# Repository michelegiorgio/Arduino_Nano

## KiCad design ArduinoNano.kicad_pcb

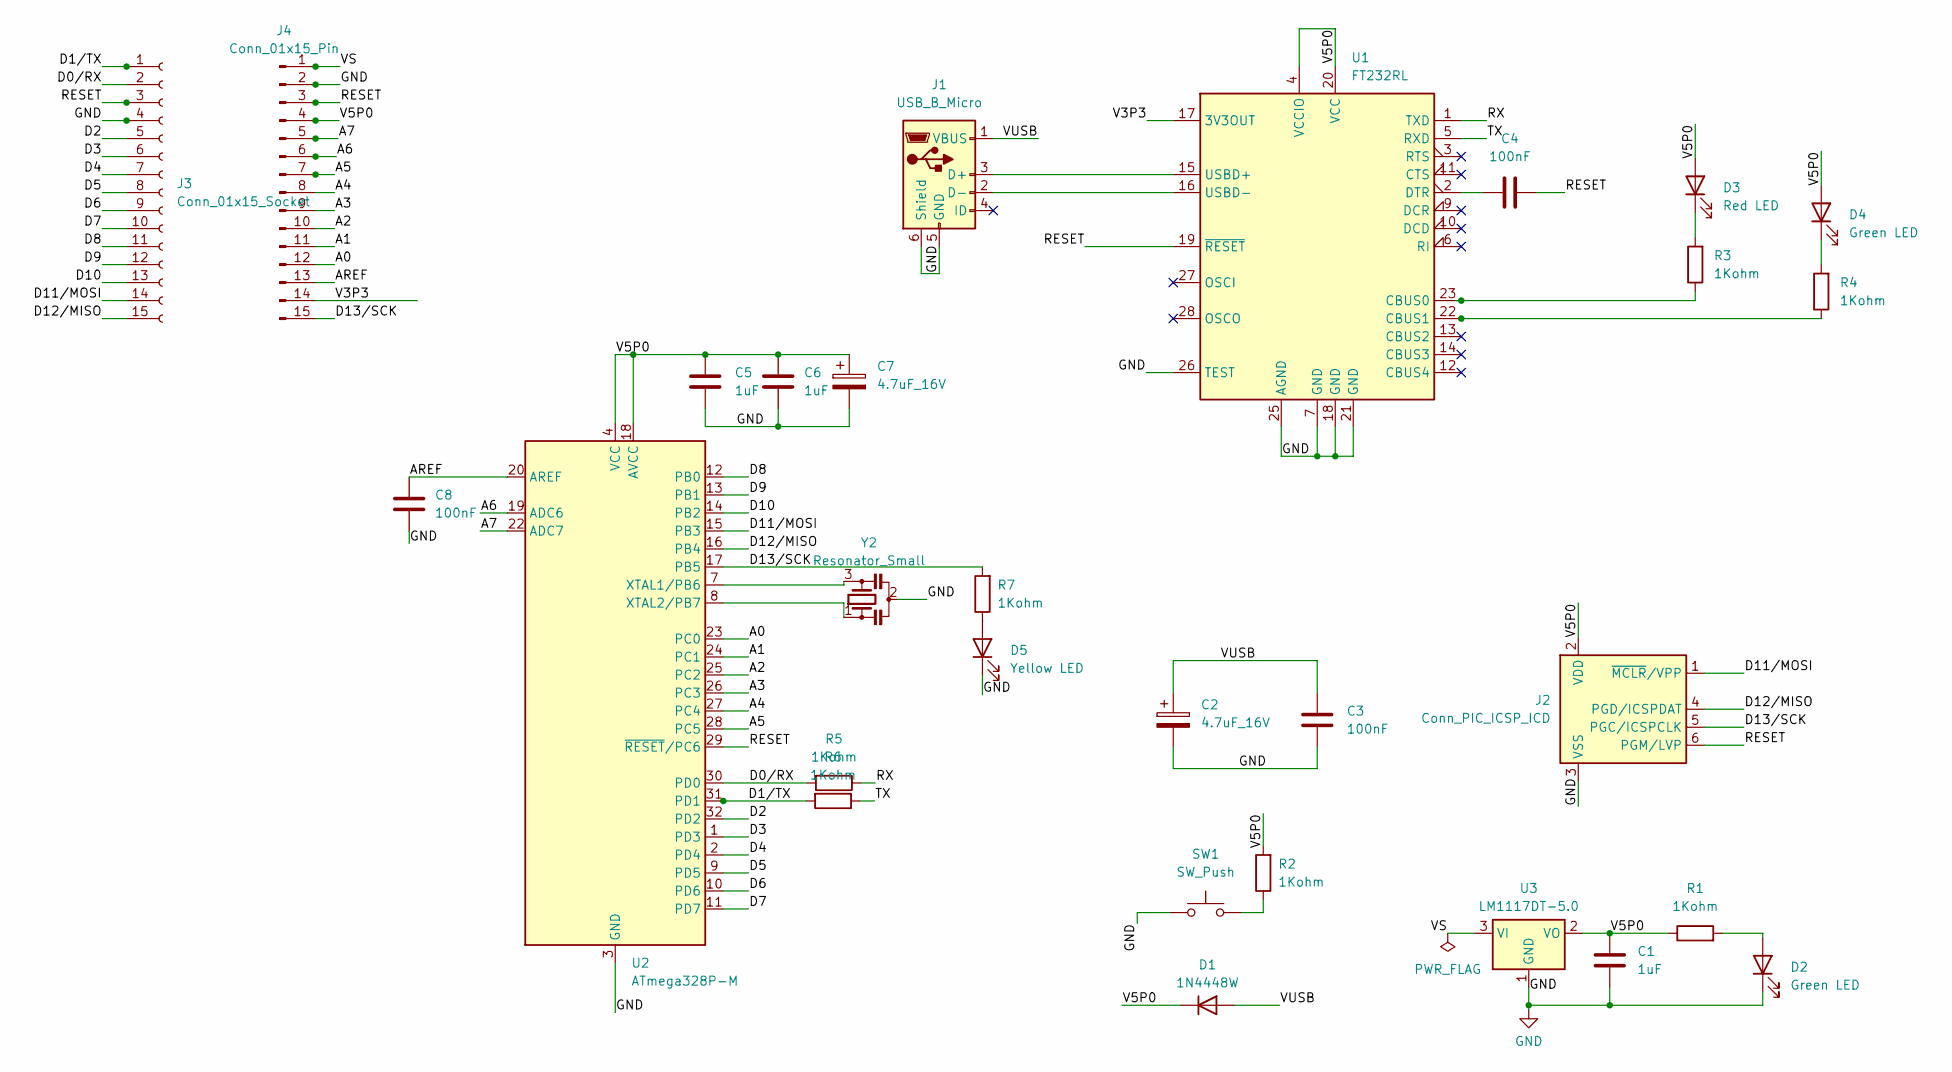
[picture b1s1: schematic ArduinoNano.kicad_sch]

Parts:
C1, C5, C6: 1uF; C_0805_2012Metric_Pad1.18x1.45mm_HandSolder
C2, C7: 4.7uF_16V; CP_EIA-3216-10_Kemet-I_Pad1.58x1.35mm_HandSolder
C3, C4, C8: 100nF; C_0805_2012Metric_Pad1.18x1.45mm_HandSolder
D1: 1N4448W; D_SOD-123
D2, D4: Green LED; LED_0603_1608Metric_Pad1.05x0.95mm_HandSolder
D3: Red LED; LED_0603_1608Metric_Pad1.05x0.95mm_HandSolder
D5: Yellow LED; LED_0603_1608Metric_Pad1.05x0.95mm_HandSolder
J1: USB_B_Micro; USB_Mini-B_Lumberg_2486_01_Horizontal
J2: Conn_PIC_ICSP_ICD; PinHeader_2x03_P2.54mm_Vertical
J3: Conn_01x15_Socket; PinHeader_1x15_P2.54mm_Vertical
J4: Conn_01x15_Pin; PinHeader_1x15_P2.54mm_Vertical
R1, R2, R3, R4, R5, R6, R7: 1Kohm; R_0805_2012Metric_Pad1.20x1.40mm_HandSolder
SW1: SW_Push; SW_Push_1P1T_NO_6x6mm_H9.5mm
U1: FT232RL; SSOP-28_5.3x10.2mm_P0.65mm
U2: ATmega328P-M; QFN-32-1EP_5x5mm_P0.5mm_EP3.1x3.1mm
U3: LM1117DT-5.0; TO-252-3_TabPin2
Y2: Resonator_Small; Crystal_SMD_3225-4Pin_3.2x2.5mm_HandSoldering

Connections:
/A0: J4.12, U2.23 (PC0)
/A1: J4.11, U2.24 (PC1)
/A2: J4.10, U2.25 (PC2)
/A3: J4.9, U2.26 (PC3)
/A4: J4.8, U2.27 (PC4)
/A5: J4.7, U2.28 (PC5)
/A6: J4.6, U2.19 (ADC6)
/A7: J4.5, U2.22 (ADC7)
/AREF: C8.1, J4.13, U2.20 (AREF)
/D0/RX: J3.2, R5.2, U2.30 (PD0)
/D1/TX: J3.1, R6.2, U2.31 (PD1)
/D2: J3.5, U2.32 (PD2)
/D3: J3.6, U2.1 (PD3)
/D4: J3.7, U2.2 (PD4)
/D5: J3.8, U2.9 (PD5)
/D6: J3.9, U2.10 (PD6)
/D7: J3.10, U2.11 (PD7)
/D8: J3.11, U2.12 (PB0)
/D9: J3.12, U2.13 (PB1)
/D10: J3.13, U2.14 (PB2)
/D11/MOSI: J2.1 (~MCLR/VPP), J3.14, U2.15 (PB3)
/D12/MISO: J2.4 (PGD/ICSPDAT), J3.15, U2.16 (PB4)
/D13/SCK: J2.5 (PGC/ICSPCLK), J4.15, R7.2, U2.17 (PB5)
/RESET: C4.2, J2.6 (PGM/LVP), J3.3, J4.3, U1.19 (~RESET), U2.29 (~RESET/PC6)
/RX: R5.1, U1.1 (TXD)
/TX: R6.1, U1.5 (RXD)
/V3P3: J4.14, U1.17 (3V3OUT)
/V5P0: C1.1, C5.1, C6.1, C7.1, D1.1 (K), D3.2 (A), D4.2 (A), J2.2 (VDD), J4.4, R1.1, R2.2, U1.4 (VCCIO), U1.20 (VCC), U2.4 (VCC), U2.6 (VCC), U2.18 (AVCC), U3.2 (VO)
/VS: J4.1, U3.3 (VI)
/VUSB: C2.1, C3.1, D1.2 (A), J1.1 (VBUS)
GND: C1.2, C2.2, C3.2, C5.2, C6.2, C7.2, C8.2, D2.1 (K), D5.1 (K), J1.5 (GND), J1.6 (Shield), J2.3 (VSS), J3.4, J4.2, SW1.1, U1.7 (GND), U1.18 (GND), U1.21 (GND), U1.25 (AGND), U1.26 (TEST), U2.3 (GND), U2.5 (GND), U2.21 (GND), U2.33 (GND), U3.1 (GND), Y2.2
unnamed: D2.2 (A), R1.2
unnamed: D3.1 (K), R3.2
unnamed: D4.1 (K), R4.2
unnamed: D5.2 (A), R7.1
unnamed: J1.3 (D+), U1.15 (USBD+)
unnamed: J1.2 (D-), U1.16 (USBD-)
unnamed: R2.1, SW1.2
unnamed: R3.1, U1.23 (CBUS0)
unnamed: R4.1, U1.22 (CBUS1)
unnamed: C4.1, U1.2 (DTR)
unnamed: U2.7 (XTAL1/PB6), Y2.3
unnamed: U2.8 (XTAL2/PB7), Y2.1

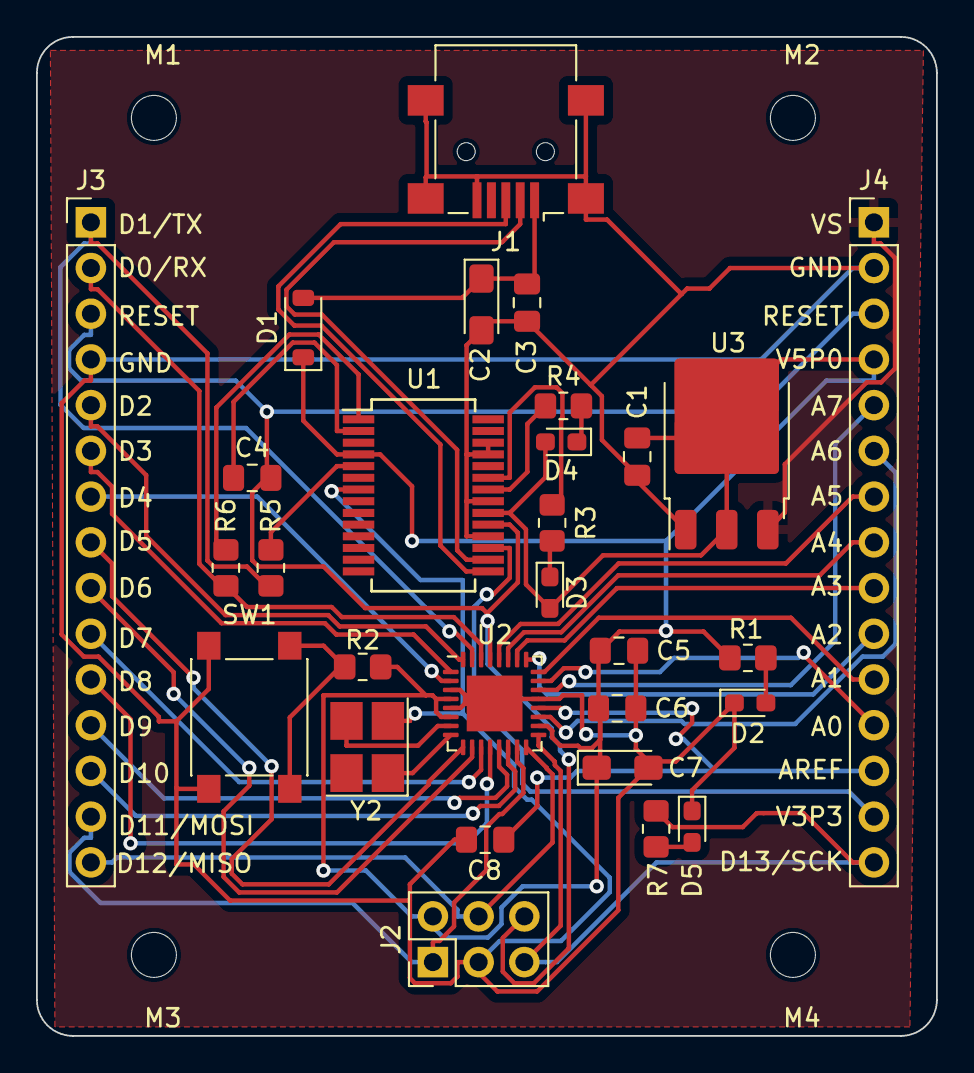
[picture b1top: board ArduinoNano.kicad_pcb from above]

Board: 2 copper layers, 50.0 x 55.5 mm, 33 parts (0 on the bottom side), 43 nets.

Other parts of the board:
M1, M2, M3, M4: MountingHole_2.5mm

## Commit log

2024-07-05 Arduino_Nano Project
